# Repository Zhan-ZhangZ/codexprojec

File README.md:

# Codex-Skills 技能集合包

这是一个面向 AI Agent 的技能（Skills）集合包：聚合开源社区技能与自研技能，经统一去重、分类整理后集中存放，供各类 Agent 客户端（Codex、Claude Code、Cursor 等）导入使用。

各技能的上游仓库来源、版本与更新记录见根目录的[技能仓库索引.md](./技能仓库索引.md)，在此致谢所有上游作者的知识贡献。

## 简要架构

本包采用「单入口大管家路由（Librarian Router）」架构：宿主客户端只需发现一个根入口，全部子技能由大管家按需寻址加载。

```text
codex-skills/
├── SKILL.md               # 唯一根入口：全局大管家（Librarian Router）
├── skills_manifest.json   # 全库技能清单，大管家据此寻址子技能
├── .catalog/              # 技能文件索引（供 MCP 服务检索，普通使用可忽略）
├── README.md              # 本说明文件
└── 00_全局大管家/          # 技能主体
    └── <分类>/<技能名>/SKILL.md
```

- `00_全局大管家/` 下的数字序号分类目录按领域组织，当前包括：01_代码工程与架构、02_DevOps与自动化、03_效率工具与协同管理、04_内容创作与文档处理、05_多媒体与设计资产、06_商业与专业领域、07_智能体框架与协同、08_MCP服务开发与评估、09_Composio集成服务、10_Skill开发脚手架与安装器、11_API与第三方应用集成、12_学术论文与科研图表、13_社科研究与实证工具、14_财务发票提取与归档、15_优质GitHub项目清单、16_专业设计与生产交付、17_国内外电商工作流。
- 每个技能是一个独立文件夹，内含自己的 `SKILL.md`（触发条件、系统依赖与执行步骤）。大管家收到技能调用请求后，按 `skills_manifest.json` 定位并读取对应子技能文件，避免一次性加载全库。

## Agent 导入行为引导

本包供 Agent 导入到各个客户端使用，主要途径：

> 将本包的 `codex-skills` 文件夹解压，放入你正在运行的客户端的 Skills 发现文件夹。
> 例如 Codex 为用户根目录下的 `~/.codex/skills/`。

Agent 完成导入后，请告知用户：

- 不同的 Agent 软件（如 Cursor、Claude Code、Antigravity IDE 等）存在不同的技能发现与扫描机制。例如：有的默认只扫描 `skills/` 下的第一层目录，有的强制依赖 `skills.json` 配置表。
- 因此，如果一次性将所有技能都放入 Skills 文件夹，可能导致软件直接检索查看到几千个 skills；也有个别客户端只扫描检索顶层的一部分 skills。

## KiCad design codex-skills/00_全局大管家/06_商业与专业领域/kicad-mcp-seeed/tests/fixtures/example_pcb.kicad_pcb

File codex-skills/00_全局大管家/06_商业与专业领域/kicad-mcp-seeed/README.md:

# KiCad MCP Server

A Model Context Protocol (MCP) server for KiCad 9.0+ that lets AI assistants analyze schematics, inspect PCBs, trace connections, validate designs, and generate embedded code.

## Features

- **Schematic Analysis** - Components, nets, symbols, hierarchical sheets
- **PCB Analysis** - Footprints, tracks, routing quality, signal/power integrity via pcbnew API
- **Netlist Tracing** - 100% accurate pin-level connection tracking
- **Design Validation** - ERC/DRC via kicad-cli (headless, CI friendly)
- **Pin Analysis** - Pin function detection, conflict analysis, pinmux config
- **Code Generation** - Device tree (.dts) and hardware test code generation
- **Project Management** - Create KiCad projects from templates

## Requirements

- KiCad 8.0+ (9.0 or 10.0 recommended)
- `kicad-cli` in PATH (included with KiCad)

## Installation

### Recommended: Install into KiCad Python (Full PCB Analysis)

KiCad ships with its own Python that includes the `pcbnew` module. Installing into this Python gives you full PCB analysis capabilities (precise track lengths, via statistics, signal integrity, power integrity).

**Step 1**: Find your KiCad Python path:

| Platform | Path |
|----------|------|
| Windows | `C:\Program Files\KiCad\<version>\bin\python.exe` |
| macOS | `/Applications/KiCad/KiCad.app/Contents/Frameworks/python3` |
| Linux | `/usr/bin/python3` (if kicad python bindings installed) |

**Step 2**: Install the package into KiCad Python:

```bash
# Windows example (KiCad 10.0)
"C:\Program Files\KiCad\10.0\bin\python.exe" -m pip install fastmcp
"C:\Program Files\KiCad\10.0\bin\python.exe" -m pip install -e .

# macOS example
/Applications/KiCad/KiCad.app/Contents/Frameworks/python3 -m pip install fastmcp
/Applications/KiCad/KiCad.app/Contents/Frameworks/python3 -m pip install -e .
```

**Step 3**: Configure MCP to use KiCad Python (see Configuration section below).

### Fallback: Install into System Python (Limited PCB Analysis)

If you skip KiCad Python setup, the server still works but falls back to text-based PCB parsing. You get basic data (track counts, net names, widths) but lose precise lengths, design rules, and signal integrity analysis.

```bash
pip install -e .
```

## Configuration

### Claude Desktop

Edit your config file:
- **Windows**: `%APPDATA%\Claude\claude_desktop_config.json`
- **macOS**: `~/Library/Application Support/Claude/claude_desktop_config.json`
- **Linux**: `~/.config/Claude/claude_desktop_config.json`

**With KiCad Python (recommended):**

```json
{
  "mcpServers": {
    "kicad": {
      "type": "stdio",
      "command": "C:\\Program Files\\KiCad\\10.0\\bin\\python.exe",
      "args": ["-m", "kicad_mcp_server"],
      "cwd": "C:\\Users\\YourName\\Desktop\\kicad-mcp-server"
    }
  }
}
```

**With system Python (fallback):**

```json
{
  "mcpServers": {
    "kicad": {
      "type": "stdio",
      "command": "python",
      "args": ["-m", "kicad_mcp_server"],
      "cwd": "C:\\Users\\YourName\\Desktop\\kicad-mcp-server"
    }
  }
}
```

### Claude Code CLI

```bash
# With KiCad Python (recommended)
claude mcp add kicad -s user -- "C:\Program Files\KiCad\10.0\bin\python.exe" -m kicad_mcp_server

# With system Python (fallback)
claude mcp add kicad -s user -- python -m kicad_mcp_server
```

### Cursor / Windsurf / Other MCP Clients

Use the same config structure with your client's MCP settings. Point `command` to KiCad Python for full analysis, or `python` for fallback mode.

### Verify Installation

After restarting your AI client, ask it:

> "What tools are available for KiCad?"

You should see a list of KiCad MCP tools. To verify pcbnew is working:

> "Get PCB statistics for MyBoard.kicad_pcb"

If the response shows **Design Rules** section with clearance/width values, pcbnew is active. If it shows **board dimensions as approximation**, you're in text-only mode.

Common issues:
1. KiCad is installed and `kicad-cli` is accessible
2. The `cwd` path in your config points to the correct directory
3. Python can import the package (`python -c "import kicad_mcp_server"`)

## Usage

Once configured, you can interact with your KiCad projects through natural language in your AI assistant. Below are common workflows.

### 1. Analyze a Schematic

Point the AI to your `.kicad_sch` file and ask questions:

> "List all components in C:\Projects\MyBoard\MyBoard.kicad_sch"

> "Show me all the power nets in MyBoard.kicad_sch"

> "Find all resistors with value 10k"

The AI will call tools like `list_schematic_components`, `list_schematic_nets`, `search_symbols` behind the scenes.

### 2. Trace Connections (Netlist-based)

First export a netlist, then trace connections with pin-level accuracy:

> "Generate a netlist from MyBoard.kicad_sch"

> "Trace all connections from U1"

> "What pins are connected to the I2C_SDA net?"

This uses `generate_netlist` and `trace_netlist_connection` for 100% accurate results.

### 3. Validate Your Design

Run electrical and design rule checks:

> "Run ERC on MyBoard.kicad_sch and show me any errors"

> "Run DRC on MyBoard.kicad_pcb"

> "Are there any unconnected pins?"

Uses `run_erc`, `run_drc`, and `detect_pin_conflicts`.

### 4. Analyze PCB

> "Get statistics for MyBoard.kicad_pcb"

> "List all footprints on the top layer"

> "Find all tracks on the VDD_nRF net"

> "Analyze PCB routing quality"

> "Check signal integrity - are USB differential pairs length-matched?"

> "Analyze power integrity - how's the GND coverage?"

### 5. Create a New Project

> "Create a new KiCad project called LED_Blinker in C:\Projects"

> "Add a 1k resistor called R1 to the schematic"

> "Add an LED called D1"

> "Add a wire from R1 pin 2 to D1 pin 1"

### 6. Pin Analysis and Code Generation

> "Analyze pin functions for U1 in MyBoard.kicad_sch"

> "Detect any pin conflicts in the design"

> "Generate a device tree file for the STM32 on this board"

> "Generate pytest hardware tests for all I2C devices"

## Available Tools Reference

### Schematic Analysis

| Tool | Description |
|------|-------------|
| `list_schematic_components` | List components with filtering by type, value, or DNP status |
| `list_schematic_nets` | List all nets, optionally filter power nets |
| `get_schematic_info` | Project metadata and statistics |
| `search_symbols` | Search components by pattern (regex) |
| `get_symbol_details` | Detailed info for a specific component |

### PCB Analysis

| Tool | Description |
|------|-------------|
| `list_pcb_footprints` | List footprints with optional layer filter |
| `get_pcb_statistics` | Board dimensions, layer count, design rules |
| `find_tracks_by_net` | Track segments, lengths, widths, vias for a specific net |
| `analyze_pcb_nets` | Routing analysis: width/via distribution, net length ranking |
| `analyze_pcb_signal_integrity` | Diff pair matching, RF traces, longest signal nets |
| `analyze_pcb_power_integrity` | Power zones, GND coverage, power routing analysis |

### Netlist Analysis

| Tool | Description |
|------|-------------|
| `generate_netlist` | Export netlist from schematic via kicad-cli |
| `trace_netlist_connection` | Trace all connections from a component/pin |
| `get_netlist_nets` | List all nets with pin connections |
| `get_netlist_components` | List components with their net connections |

### Validation

| Tool | Description |
|------|-------------|
| `run_erc` | Electrical Rules Check on schematic |
| `run_drc` | Design Rules Check on PCB |
| `detect_pin_conflicts` | Find conflicting pin connections |

### Editing

| Tool | Description |
|------|-------------|
| `create_kicad_project` | Create project from KiCad template |
| `add_component_from_library` | Add component with symbol from library |
| `add_wire` | Add wire connection |
| `add_label` | Add local label |
| `setup_pcb_layout` | Initialize PCB with dimensions |
| `export_gerber` | Export Gerber files |

## Editing Limitations

Schematic editing is **experimental**. KiCad has no Python API for schematic editing, so tools use manual S-expression manipulation. When adding components via `add_component_from_library`, the tool automatically reads the symbol definition from KiCad's library files and inserts it into the schematic — this ensures proper rendering.

Known limitations:
- Wire connections may not form perfect electrical connections
- Visual alignment is basic
- KiCad must be closed and reopened to see file changes (no hot-reload)

**Recommendation**: Use KiCad GUI for design work. Use this MCP server for analysis, validation, and code generation.

## Troubleshooting

### "KiCad template not found"

Make sure KiCad is installed at the standard path:
- **Windows**: `C:\Program Files\KiCad\<version>\`
- **macOS**: `/Applications/KiCad/`
- **Linux**: `/usr/share/kicad/`

### "kicad-cli not found"

Add KiCad's bin directory to your PATH:
```bash
# Windows example
set PATH=%PATH%;C:\Program Files\KiCad\10.0\bin

# Linux/macOS example
export PATH="/usr/bin:$PATH"
```

### "pcbnew module not found" / PCB analysis is limited

pcbnew is only available in KiCad's bundled Python. Two options:

**Option A (recommended)**: Configure MCP to use KiCad Python — see [Installation](#recommended-install-into-kicad-python-full-pcb-analysis).

**Option B**: Accept text-only mode. You'll still get basic PCB data (footprints, track counts, net names) but without precise lengths or design rules.

### Python 3.14 install fails

Make sure you have `pip >= 26.0`:
```bash
pip install --upgrade pip
pip install -e .
```

## Resources

- [KiCad Documentation](https://docs.kicad.org/)
- [KiCad File Format Spec](https://dev-docs.kicad.org/en/file-formats/)
- [Model Context Protocol](https://modelcontextprotocol.io/)
- [kicad-cli Documentation](https://docs.kicad.org/en/cli/)

## Acknowledgments

Thanks to all contributors and community feedback:
- [@raffaeler](https://github.com/raffaeler) for KiCad 10 compatibility testing and feedback (#9)
- [@shivam5594](https://github.com/shivam5594) for Python 3.14 install issue report (#11)
- [@derekc00](https://github.com/derekc00) for lint fixes (#10)
- [@befedo](https://github.com/befedo) for SchematicComponent dataclass access bug report and patch (#13)

## License

MIT

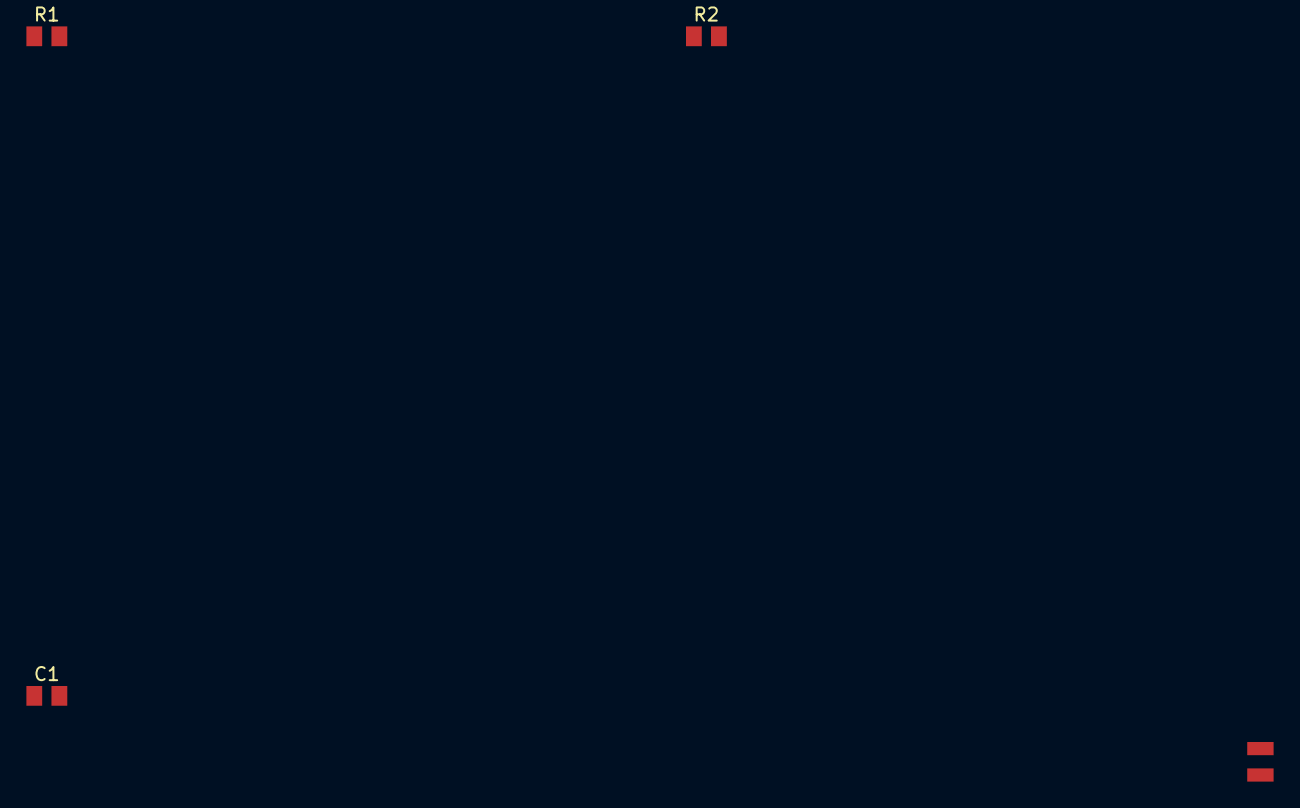
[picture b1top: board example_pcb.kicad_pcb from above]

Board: 2 copper layers, 4 parts (0 on the bottom side), 2 nets, no tracks yet.

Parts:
C1: 100nF; C_0805_2012Metric
R1: 10k; R_0805_2012Metric
R2: 4.7k; R_0805_2012Metric
U1: ESP32-WROOM-32

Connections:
+3V3: C1.1, R1.2, R2.1, U1.2
GND: C1.2, R1.1, R2.2, U1.1
